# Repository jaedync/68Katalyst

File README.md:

# 68Katalyst

68Katalyst is a computer engineering project at Letourneau University. The goal is to create a turing complete 68k microcomputer that can commnicate over a serial connection.'

## Software used

- [KiCad](https://www.kicad.org/) PCB design software

## Contact Information

If you have any questions, feel free to reach out at me@jaedynchilton.com!

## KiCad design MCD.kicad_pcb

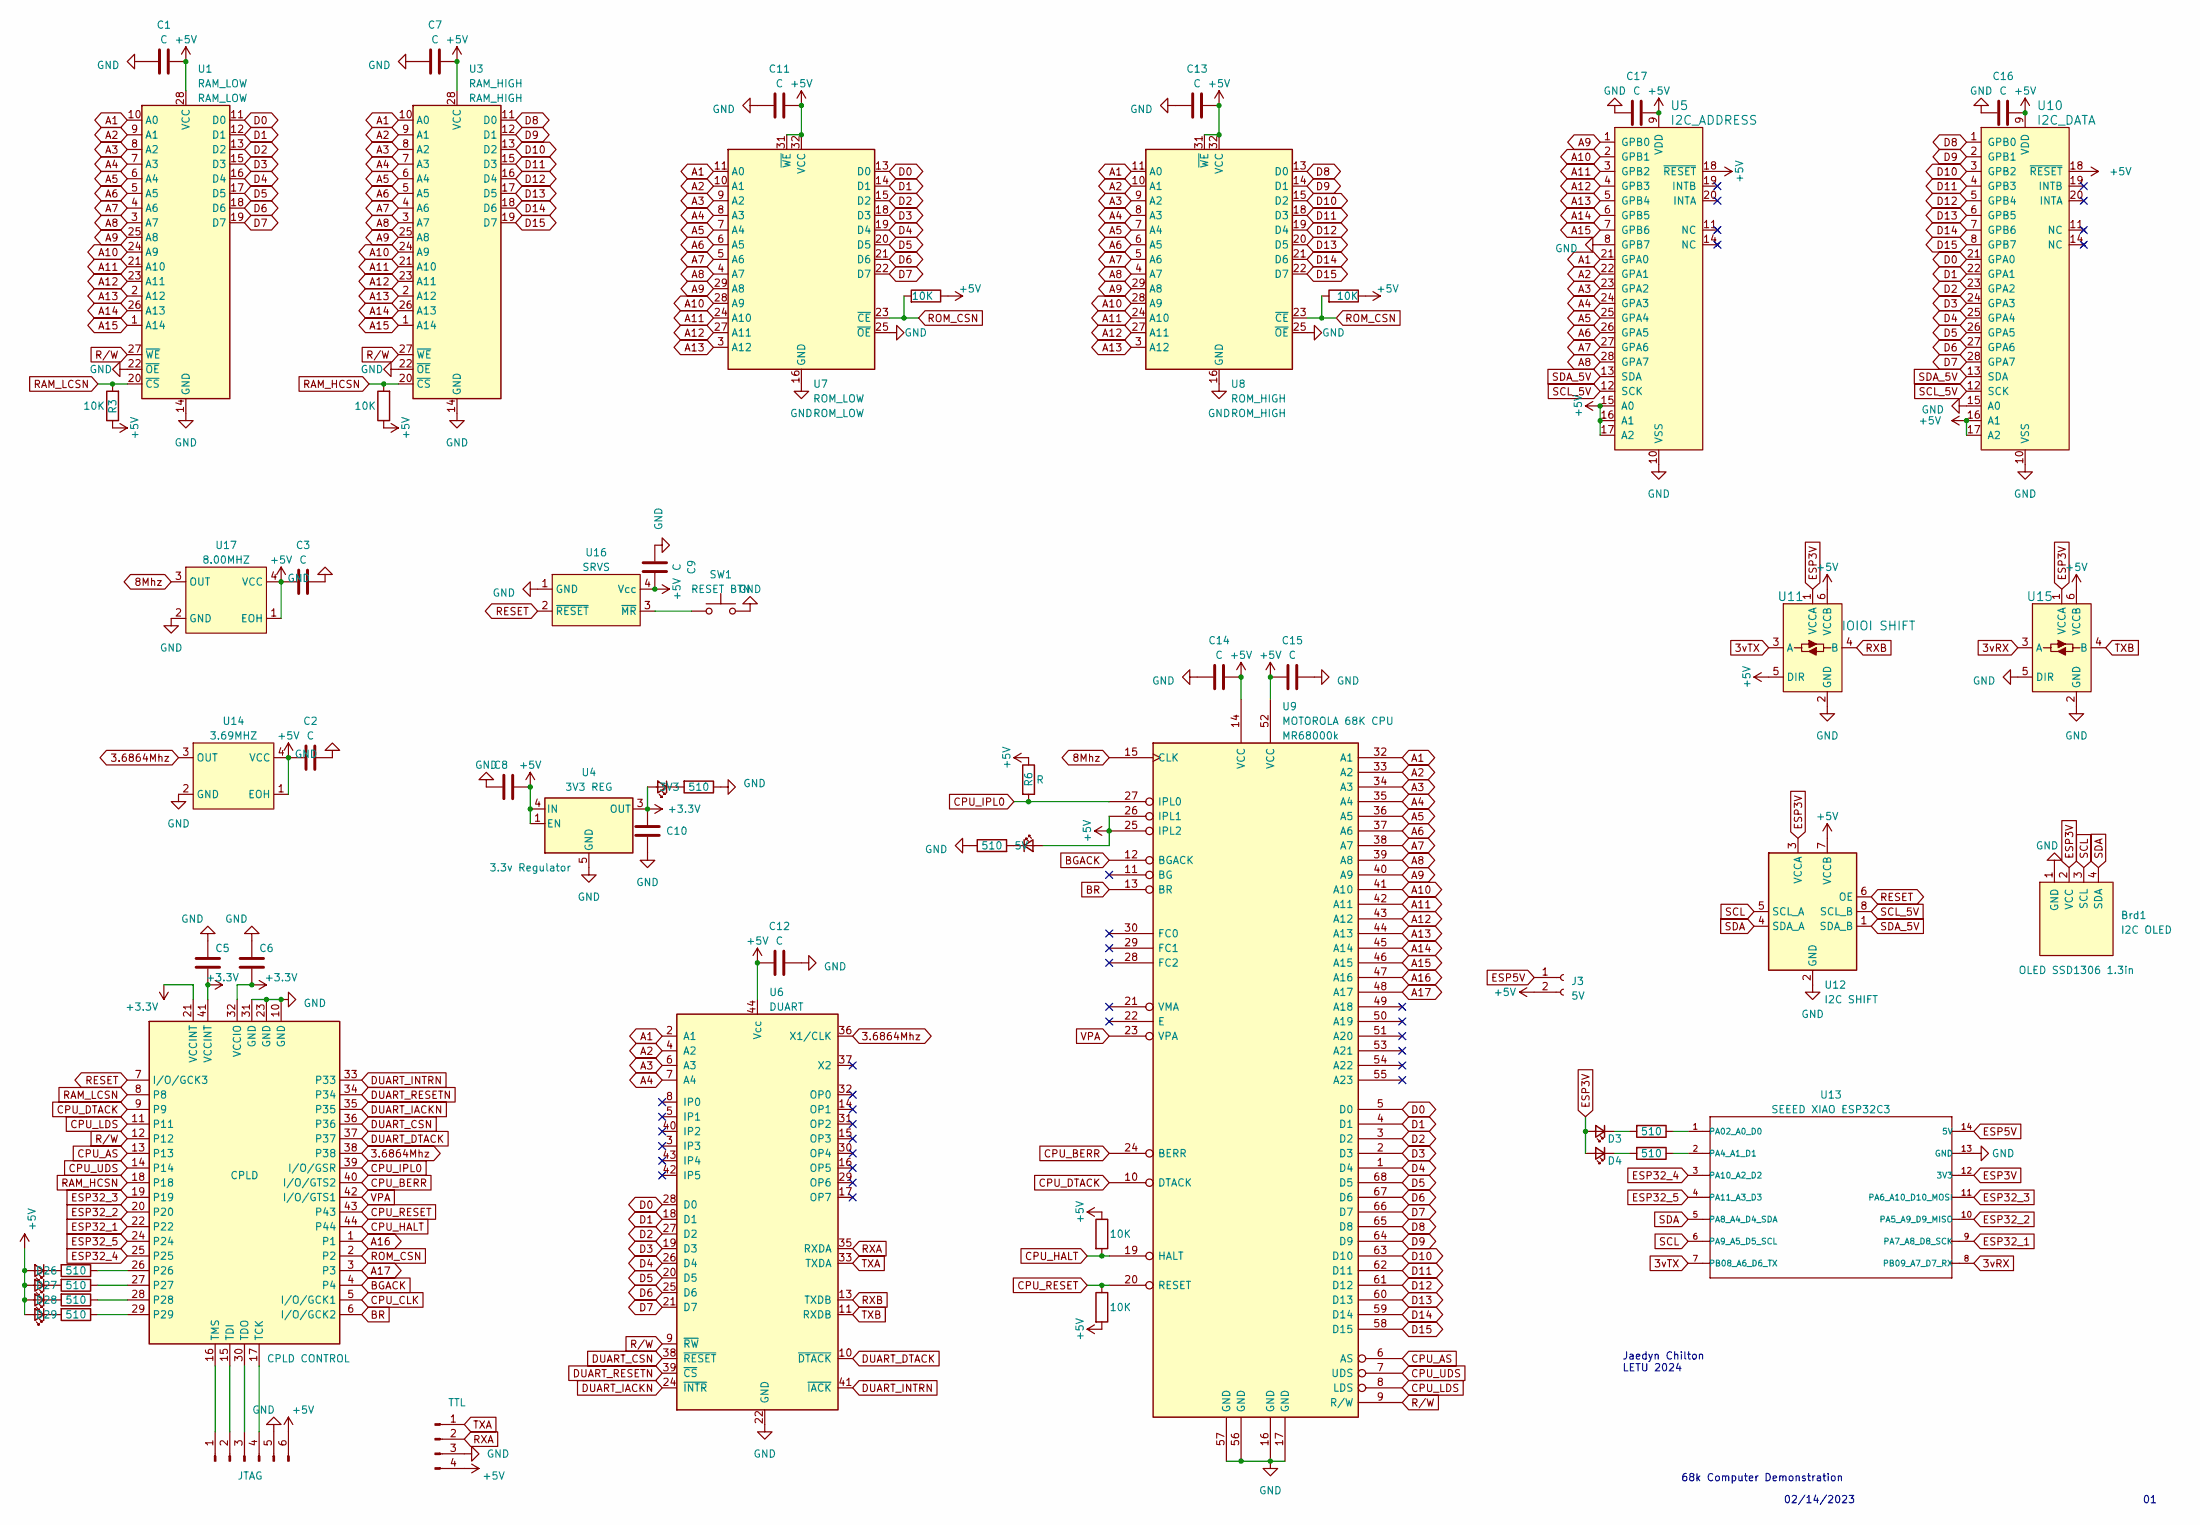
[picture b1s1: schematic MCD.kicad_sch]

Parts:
Brd1: I2C OLED; 128x64OLED
C1, C2, C3, C5, C6, C7, C8, C9, C10, C11, C12, C13, C14, C15, C16, C17: C; C_0805_2012Metric_Pad1.18x1.45mm_HandSolder
D1: D26; LED_0805_2012Metric_Pad1.15x1.40mm_HandSolder
D2: D27; LED_0805_2012Metric_Pad1.15x1.40mm_HandSolder
D3, D4: Green; LED_0805_2012Metric_Pad1.15x1.40mm_HandSolder
D5: 5V; LED_0805_2012Metric_Pad1.15x1.40mm_HandSolder
D6: 3V3; LED_0805_2012Metric_Pad1.15x1.40mm_HandSolder
D28: D28; LED_0805_2012Metric_Pad1.15x1.40mm_HandSolder
D29: D29; LED_0805_2012Metric_Pad1.15x1.40mm_HandSolder
J1: JTAG; PinSocket_1x06_P2.54mm_Vertical
J2: TTL; PinSocket_1x04_P2.54mm_Vertical
J3: 5V; PinSocket_1x02_P2.54mm_Vertical
R1, R2, R10, R11: 510; R_0805_2012Metric_Pad1.20x1.40mm_HandSolder
R3, R4, R5, R7, R8, R9: 10K; R_0805_2012Metric_Pad1.20x1.40mm_HandSolder
R6: R; R_0805_2012Metric_Pad1.20x1.40mm_HandSolder
Re1, Re2, Re3, Re4: 510; R_0805_2012Metric_Pad1.20x1.40mm_HandSolder
SW1: RESET BTN; SW_Push_1P1T_NO_6x6mm_H9.5mm
U1: RAM_LOW; RAM
U2: CPLD CONTROL; PLCC-44_THT-Socket
U3: RAM_HIGH; RAM
U4: 3V3 REG; SOT-223-5
U5: I2C_ADDRESS; i2c; MPN MCP23017-E/SO; Digi-Key_PN MCP23017-E/SO-ND
U6: DUART; PLCC-44_THT-Socket
U7: ROM_LOW; PLCC-32_THT-Socket
U8: ROM_HIGH; PLCC-32_THT-Socket
U9: MOTOROLA 68K CPU; PLCC-68_THT-Socket
U10: I2C_DATA; i2c; MPN MCP23017-E/SO; Digi-Key_PN MCP23017-E/SO-ND
U11, U15: IOIOI SHIFT; SOT-363; MPN SN74LVC1T45DBVR; Digi-Key_PN 296-16843-1-ND
U12: I2C SHIFT; SSOP-8_2.95x2.8mm_P0.65mm
U13: SEEED XIAO ESP32C3; MOUDLE14P-SMD-2.54-21X17.8MM
U14: 3.69MHZ; Oscillator_SMD_SeikoEpson_SG8002CA-4Pin_7.0x5.0mm_HandSolde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
U16: SRVS; SOT-143_Handsoldering
U17: 8.00MHZ; Oscillator_SMD_SeikoEpson_SG8002CA-4Pin_7.0x5.0mm_HandSolde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

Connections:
3.6864Mhz: U2.38, U6.36 (X1/CLK), U14.3 (OUT)
3vRX: U13.8 (PB09_A7_D7_RX), U15.3 (A)
3vTX: U11.3 (A), U13.7 (PB08_A6_D6_TX)
8Mhz: U9.15 (CLK), U17.3 (OUT)
+3.3V: C5.1, C6.1, C10.2, D6.2 (A), U2.21 (VCCINT), U2.32 (VCCIO), U2.41 (VCCINT), U4.3 (OUT)
+5V: C1.1, C2.2, C3.2, C7.1, C8.1, C9.1, C11.1, C12.1, C13.1, C14.1, C15.1, C16.1, C17.1, D1.2 (A), D2.2 (A), D5.2 (A), D28.2 (A), D29.2 (A), J1.6, J2.4, J3.2, R3.1, R4.1, R5.1, R6.1, R7.1, R8.2, R9.1, U1.28 (VCC), U3.28 (VCC), U4.1 (EN), U4.4 (IN), U5.9 (VDD), U5.15 (A0), U5.16 (A1), U5.17 (A2), U5.18 (~RESET), U6.44 (Vcc), U7.31 (~WE), U7.32 (VCC), U8.31 (~WE), U8.32 (VCC), U9.14 (VCC), U9.25 (IPL2), U9.26 (IPL1), U9.52 (VCC), U10.9 (VDD), U10.16 (A1), U10.17 (A2), U10.18 (~RESET), U11.5 (DIR), U11.6 (VCCB), U12.7 (VCCB), U14.1 (EOH), U14.4 (VCC), U15.6 (VCCB), U16.4 (Vcc), U17.1 (EOH), U17.4 (VCC)
A1: U1.10 (A0), U3.10 (A0), U5.21 (GPA0), U6.2 (A1), U7.11 (A0), U8.11 (A0), U9.32 (A1)
A2: U1.9 (A1), U3.9 (A1), U5.22 (GPA1), U6.4 (A2), U7.10 (A1), U8.10 (A1), U9.33 (A2)
A3: U1.8 (A2), U3.8 (A2), U5.23 (GPA2), U6.6 (A3), U7.9 (A2), U8.9 (A2), U9.34 (A3)
A4: U1.7 (A3), U3.7 (A3), U5.24 (GPA3), U6.7 (A4), U7.8 (A3), U8.8 (A3), U9.35 (A4)
A5: U1.6 (A4), U3.6 (A4), U5.25 (GPA4), U7.7 (A4), U8.7 (A4), U9.36 (A5)
A6: U1.5 (A5), U3.5 (A5), U5.26 (GPA5), U7.6 (A5), U8.6 (A5), U9.37 (A6)
A7: U1.4 (A6), U3.4 (A6), U5.27 (GPA6), U7.5 (A6), U8.5 (A6), U9.38 (A7)
A8: U1.3 (A7), U3.3 (A7), U5.28 (GPA7), U7.4 (A7), U8.4 (A7), U9.39 (A8)
A9: U1.25 (A8), U3.25 (A8), U5.1 (GPB0), U7.29 (A8), U8.29 (A8), U9.40 (A9)
A10: U1.24 (A9), U3.24 (A9), U5.2 (GPB1), U7.28 (A9), U8.28 (A9), U9.41 (A10)
A11: U1.21 (A10), U3.21 (A10), U5.3 (GPB2), U7.24 (A10), U8.24 (A10), U9.42 (A11)
A12: U1.23 (A11), U3.23 (A11), U5.4 (GPB3), U7.27 (A11), U8.27 (A11), U9.43 (A12)
A13: U1.2 (A12), U3.2 (A12), U5.5 (GPB4), U7.3 (A12), U8.3 (A12), U9.44 (A13)
A14: U1.26 (A13), U3.26 (A13), U5.6 (GPB5), U9.45 (A14)
A15: U1.1 (A14), U3.1 (A14), U5.7 (GPB6), U9.46 (A15)
A16: U2.1, U9.47 (A16)
A17: U2.3, U9.48 (A17)
BGACK: U2.4, U9.12 (BGACK)
BR: U2.6 (I/O/GCK2), U9.13 (BR)
CPU_AS: U2.13, U9.6 (AS)
CPU_BERR: U2.40 (I/O/GTS2), U9.24 (BERR)
CPU_CLK: U2.5 (I/O/GCK1)
CPU_DTACK: U2.9, U9.10 (DTACK)
CPU_HALT: R7.2, U2.44, U9.19 (HALT)
CPU_IPL0: R6.2, U2.39 (I/O/GSR), U9.27 (IPL0)
CPU_LDS: U2.11, U9.8 (LDS)
CPU_RESET: R8.1, U2.43, U9.20 (RESET)
CPU_UDS: U2.14, U9.7 (UDS)
D0: U1.11 (D0), U6.28 (D0), U7.13 (D0), U9.5 (D0), U10.21 (GPA0)
D1: U1.12 (D1), U6.18 (D1), U7.14 (D1), U9.4 (D1), U10.22 (GPA1)
D2: U1.13 (D2), U6.27 (D2), U7.15 (D2), U9.3 (D2), U10.23 (GPA2)
D3: U1.15 (D3), U6.19 (D3), U7.18 (D3), U9.2 (D3), U10.24 (GPA3)
D4: U1.16 (D4), U6.26 (D4), U7.19 (D4), U9.1 (D4), U10.25 (GPA4)
D5: U1.17 (D5), U6.20 (D5), U7.20 (D5), U9.68 (D5), U10.26 (GPA5)
D6: U1.18 (D6), U6.25 (D6), U7.21 (D6), U9.67 (D6), U10.27 (GPA6)
D7: U1.19 (D7), U6.21 (D7), U7.22 (D7), U9.66 (D7), U10.28 (GPA7)
D8: U3.11 (D0), U8.13 (D0), U9.65 (D8), U10.1 (GPB0)
D9: U3.12 (D1), U8.14 (D1), U9.64 (D9), U10.2 (GPB1)
D10: U3.13 (D2), U8.15 (D2), U9.63 (D10), U10.3 (GPB2)
D11: U3.15 (D3), U8.18 (D3), U9.62 (D11), U10.4 (GPB3)
D12: U3.16 (D4), U8.19 (D4), U9.61 (D12), U10.5 (GPB4)
D13: U3.17 (D5), U8.20 (D5), U9.60 (D13), U10.6 (GPB5)
D14: U3.18 (D6), U8.21 (D6), U9.59 (D14), U10.7 (GPB6)
D15: U3.19 (D7), U8.22 (D7), U9.58 (D15), U10.8 (GPB7)
DUART_CSN: U2.36, U6.38 (~RESET)
DUART_DTACK: U2.37, U6.10 (~DTACK)
DUART_IACKN: U2.35, U6.24 (~INTR)
DUART_INTRN: U2.33, U6.41 (~IACK)
DUART_RESETN: U2.34, U6.39 (~CS)
ESP3V: Brd1.2 (VCC), D3.2 (A), D4.2 (A), U11.1 (VCCA), U12.3 (VCCA), U13.12 (3V3), U15.1 (VCCA)
ESP5V: J3.1, U13.14 (5V)
ESP32_1: U2.22, U13.9 (PA7_A8_D8_SCK)
ESP32_2: U2.20, U13.10 (PA5_A9_D9_MISO)
ESP32_3: U2.19, U13.11 (PA6_A10_D10_MOSI)
ESP32_4: U2.25, U13.3 (PA10_A2_D2)
ESP32_5: U2.24, U13.4 (PA11_A3_D3)
GND: Brd1.1 (GND), C1.2, C2.1, C3.1, C5.2, C6.2, C7.2, C8.2, C9.2, C10.1, C11.2, C12.2, C13.2, C14.2, C15.2, C16.2, C17.2, J1.5, J2.3, Re3.1, Re4.1, SW1.2, U1.14 (GND), U1.22 (~OE), U2.10 (GND), U2.23 (GND), U2.31 (GND), U3.14 (GND), U3.22 (~OE), U4.5 (GND), U5.8 (GPB7), U5.10 (VSS), U6.22 (GND), U7.16 (GND), U7.25 (~OE), U8.16 (GND), U8.25 (~OE), U9.16 (GND), U9.17 (GND), U9.56 (GND), U9.57 (GND), U10.10 (VSS), U10.15 (A0), U11.2 (GND), U12.2 (GND), U13.13 (GND), U14.2 (GND), U15.2 (GND), U15.5 (DIR), U16.1 (GND), U17.2 (GND)
unnamed: D1.1 (K), R2.2
unnamed: D2.1 (K), Re2.2
unnamed: D3.1 (K), R10.2
unnamed: D4.1 (K), R11.2
unnamed: D5.1 (K), Re3.2
unnamed: D6.1 (K), Re4.2
unnamed: D28.1 (K), R1.2
unnamed: D29.1 (K), Re1.2
unnamed: J1.1, U2.16 (TMS)
unnamed: J1.2, U2.15 (TDI)
unnamed: J1.3, U2.30 (TDO)
unnamed: J1.4, U2.17 (TCK)
unnamed: R2.1, U2.26
unnamed: Re2.1, U2.27
unnamed: R1.1, U2.28
unnamed: Re1.1, U2.29
unnamed: R10.1, U13.1 (PA02_A0_D0)
unnamed: R11.1, U13.2 (PA4_A1_D1)
unnamed: SW1.1, U16.3 (~MR)
RAM_HCSN: R4.2, U2.18, U3.20 (~CS)
RAM_LCSN: R3.2, U1.20 (~CS), U2.8
RESET: U2.7 (I/O/GCK3), U12.6 (OE), U16.2 (~RESET)
ROM_CSN: R5.2, R9.2, U2.2, U7.23 (~CE), U8.23 (~CE)
RXA: J2.2, U6.35 (RXDA)
RXB: U6.13 (TXDB), U11.4 (B)
R/W: U1.27 (~WE), U2.12, U3.27 (~WE), U6.9 (~RW), U9.9 (R/W)
SCL: Brd1.3 (SCL), U12.5 (SCL_A), U13.6 (PA9_A5_D5_SCL)
SCL_5V: U5.12 (SCK), U10.12 (SCK), U12.8 (SCL_B)
SDA: Brd1.4 (SDA), U12.4 (SDA_A), U13.5 (PA8_A4_D4_SDA)
SDA_5V: U5.13 (SDA), U10.13 (SDA), U12.1 (SDA_B)
TXA: J2.1, U6.33 (TXDA)
TXB: U6.11 (RXDB), U15.4 (B)
VPA: U2.42 (I/O/GTS1), U9.23 (VPA)

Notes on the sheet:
Jaedyn Chilton LETU 2024
02/14/2023
68k Computer Demonstration

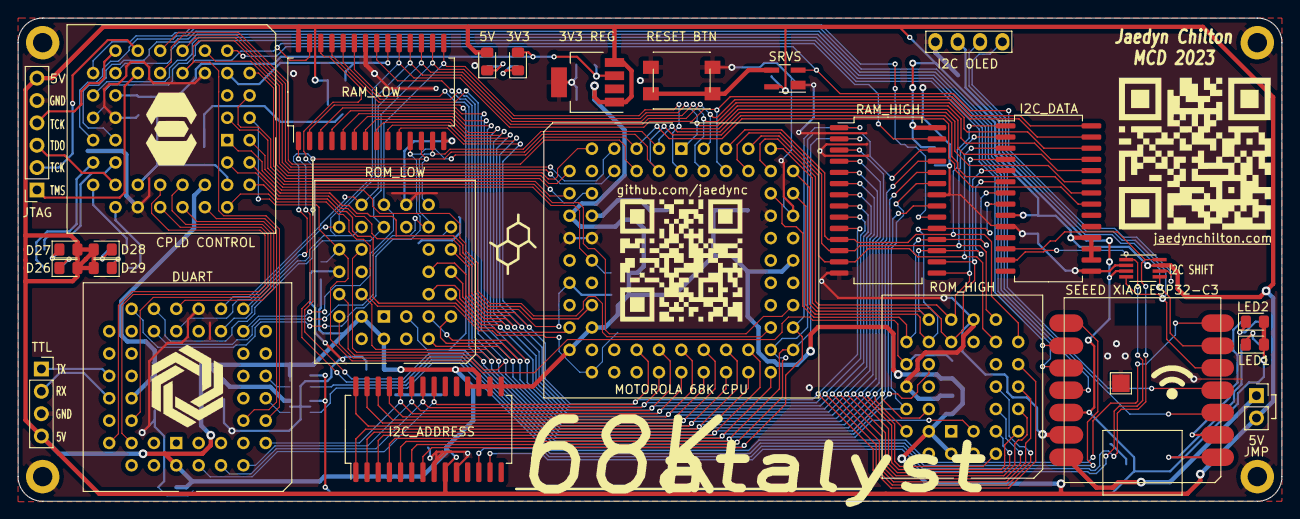
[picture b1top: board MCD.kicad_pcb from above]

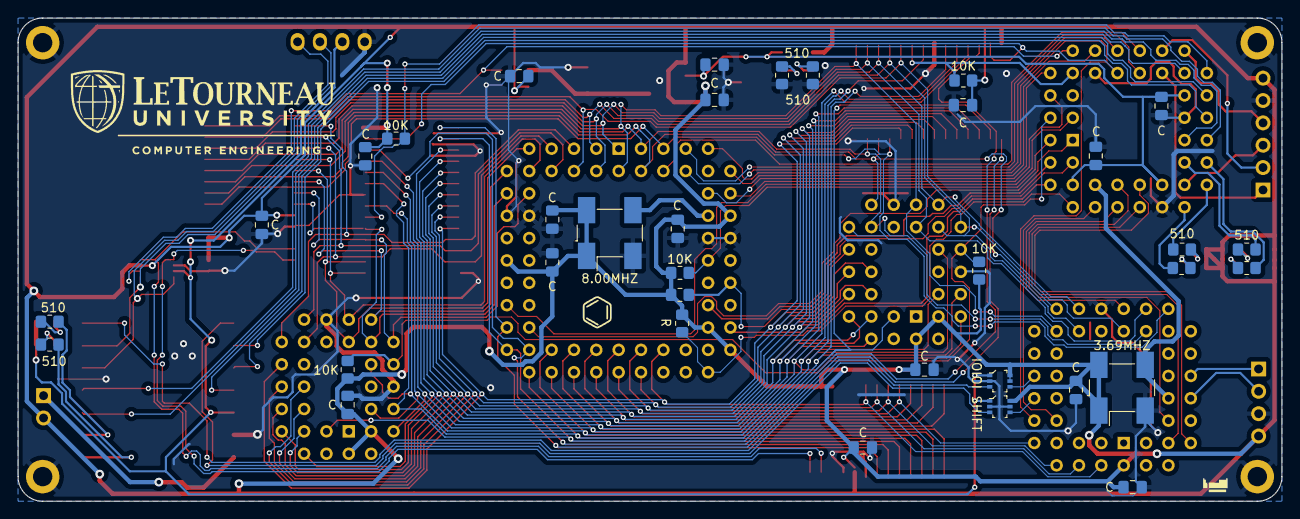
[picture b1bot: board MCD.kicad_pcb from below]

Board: 2 copper layers, 143.6 x 54.9 mm, 61 parts (35 on the bottom side), 95 nets.

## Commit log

2023-03-03 68Katalyst 1.0
    First revision of board.
2023-03-04 Rev 1.1
    Added pictures of PCB and readme
2023-04-28 Software
    Completed Software Upload
